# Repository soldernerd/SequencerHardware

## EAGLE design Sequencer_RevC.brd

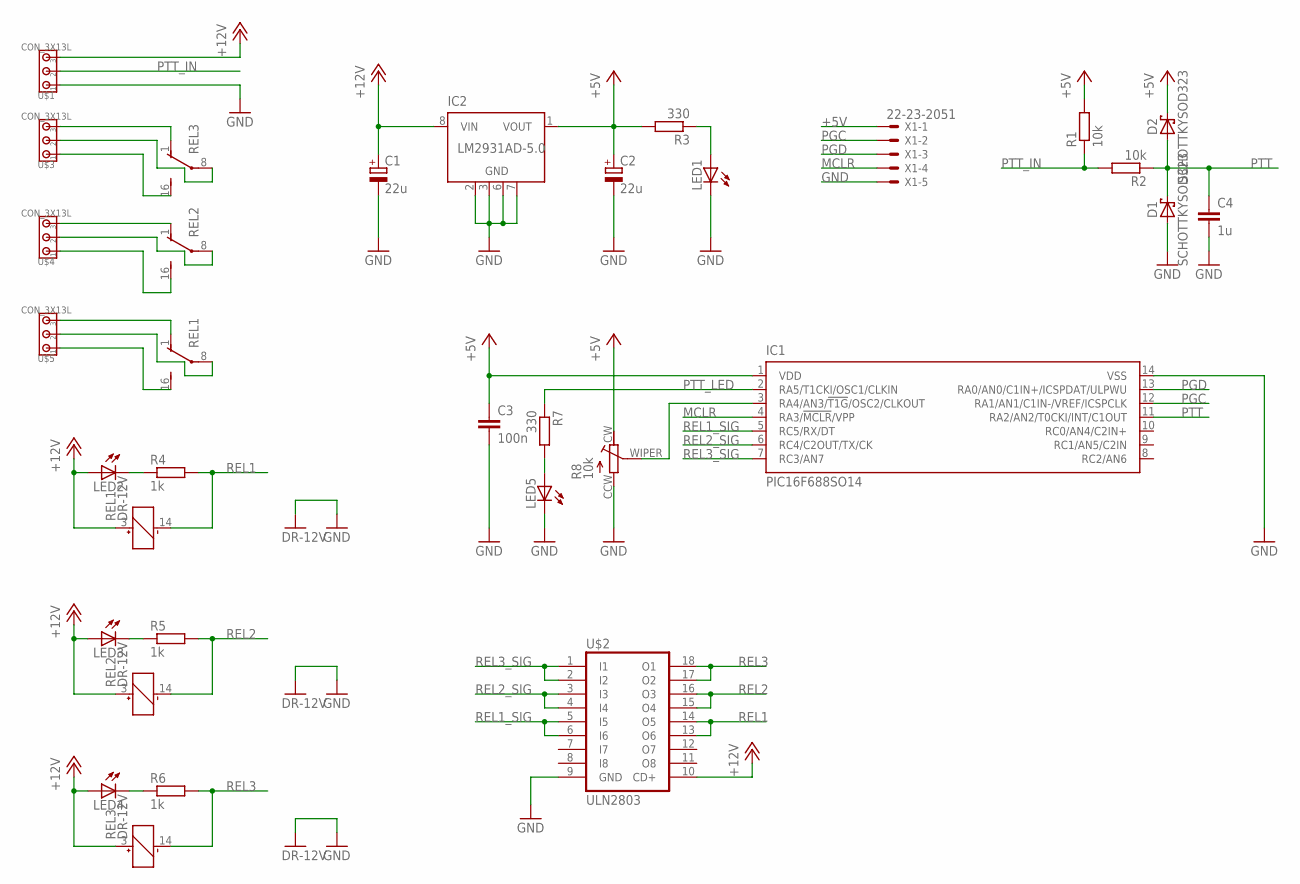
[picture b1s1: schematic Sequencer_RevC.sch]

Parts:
C1, C2: 22u; SMC_C
C3: 100n; C0805
C4: 1u; C0805
D1, D2: SCHOTTKYSOD323; SOD323
IC1: PIC16F688SO14; SO14
IC2: LM2931AD-5.0; SO8
LED1, LED2, LED3, LED4, LED5: LED0805
R1, R2: 10k; R0805
R3, R7: 330; R0805
R4, R5, R6: 1k; R0805
R8: 10k; RTRIM3314G
REL1, REL2, REL3: DR-12V
U$1, U$3, U$4, U$5: CON_3X13L; 200MIL_3X
U$2: ULN2803; SO18W
X1: 22-23-2051

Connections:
+5V: C2.+, C3.1, D2.C, IC1.1 (VDD), IC2.1 (VOUT), R1.2, R3.2, R8.CW, X1.1
+12V: C1.+, IC2.8 (VIN), LED2.A, LED3.A, LED4.A, REL1.3 (+), REL2.3 (+), REL3.3 (+), U$1.3, U$2.10 (CD+)
GND: C1.-, C2.-, C3.2, C4.2, D1.A, IC1.14 (VSS), IC2.2 (GND), IC2.3 (GND), IC2.6 (GND), IC2.7 (GND), LED1.C, LED5.C, R8.CCW, REL1.9 (GND), REL2.9 (GND), REL3.9 (GND), U$1.1, U$2.9 (GND), X1.5
MCLR: IC1.4 (RA3/!MCLR!/VPP), X1.4
unnamed: REL2.16 (S), U$4.1
unnamed: REL2.8, U$4.2
unnamed: REL2.1 (O), U$4.3
unnamed: REL3.8, U$3.2
unnamed: REL1.8, U$5.2
unnamed: REL1.16 (S), U$5.1
unnamed: REL3.16 (S), U$3.1
unnamed: REL3.1 (O), U$3.3
unnamed: IC1.3 (RA4/AN3/!T1G!/OSC2/CLKOUT), R8.WIPER
unnamed: LED1.A, R3.1
unnamed: LED5.A, R7.2
unnamed: REL1.1 (O), U$5.3
unnamed: LED3.C, R5.1
unnamed: LED2.C, R4.1
unnamed: LED4.C, R6.1
PGC: IC1.12 (RA1/AN1/C1IN-/VREF/ICSPCLK), X1.2
PGD: IC1.13 (RA0/AN0/C1IN+/ICSPDAT/ULPWU), X1.3
PTT: C4.1, D1.C, D2.A, IC1.11 (RA2/AN2/T0CKI/INT/C1OUT), R2.1
PTT_IN: R1.1, R2.2, U$1.2
PTT_LED: IC1.2 (RA5/T1CKI/OSC1/CLKIN), R7.1
REL1: R4.2, REL1.14 (-), U$2.13 (O6), U$2.14 (O5)
REL1_SIG: IC1.5 (RC5/RX/DT), U$2.5 (I5), U$2.6 (I6)
REL2: R5.2, REL2.14 (-), U$2.15 (O4), U$2.16 (O3)
REL2_SIG: IC1.6 (RC4/C2OUT/TX/CK), U$2.3 (I3), U$2.4 (I4)
REL3: R6.2, REL3.14 (-), U$2.17 (O2), U$2.18 (O1)
REL3_SIG: IC1.7 (RC3/AN7), U$2.1 (I1), U$2.2 (I2)

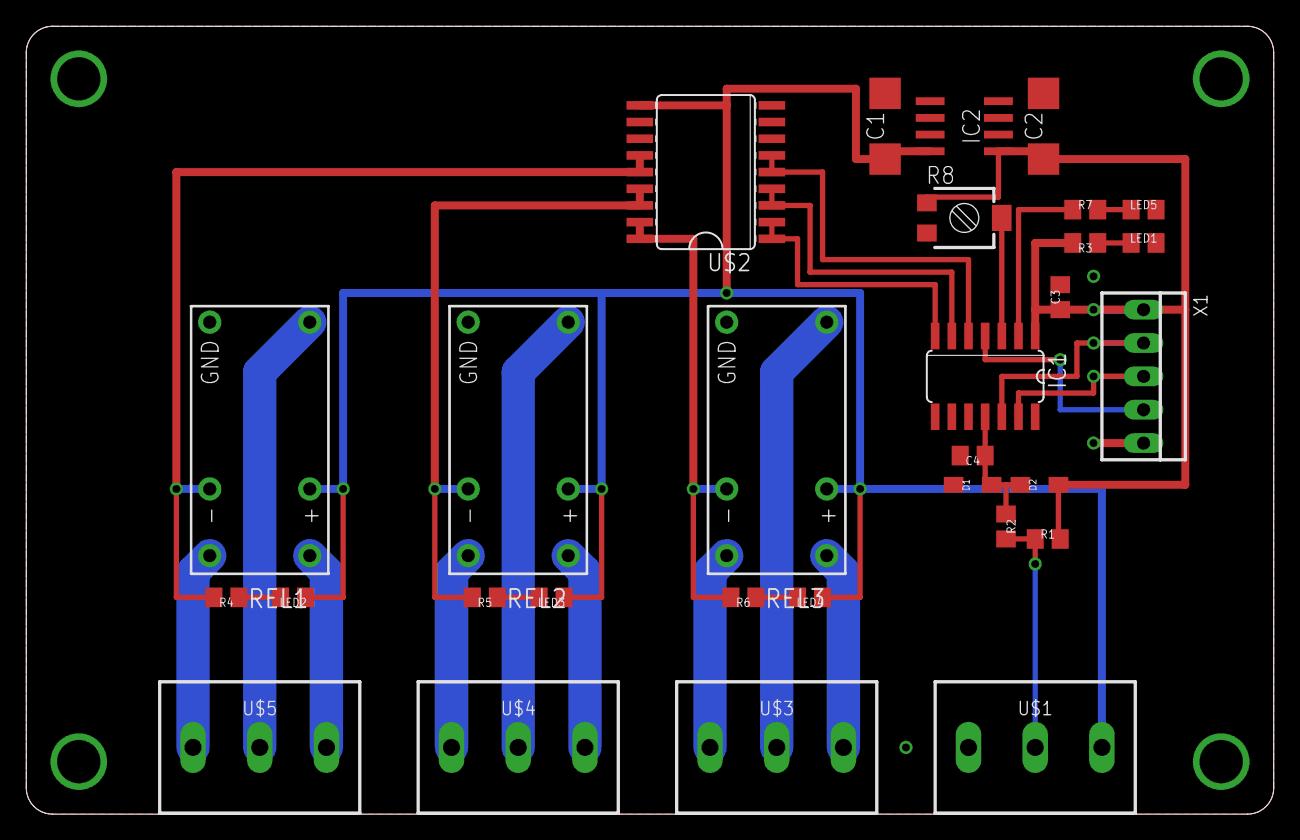
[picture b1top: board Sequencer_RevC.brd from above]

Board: 2 copper layers, 95.0 x 60.0 mm, 30 parts (0 on the bottom side), 30 nets.

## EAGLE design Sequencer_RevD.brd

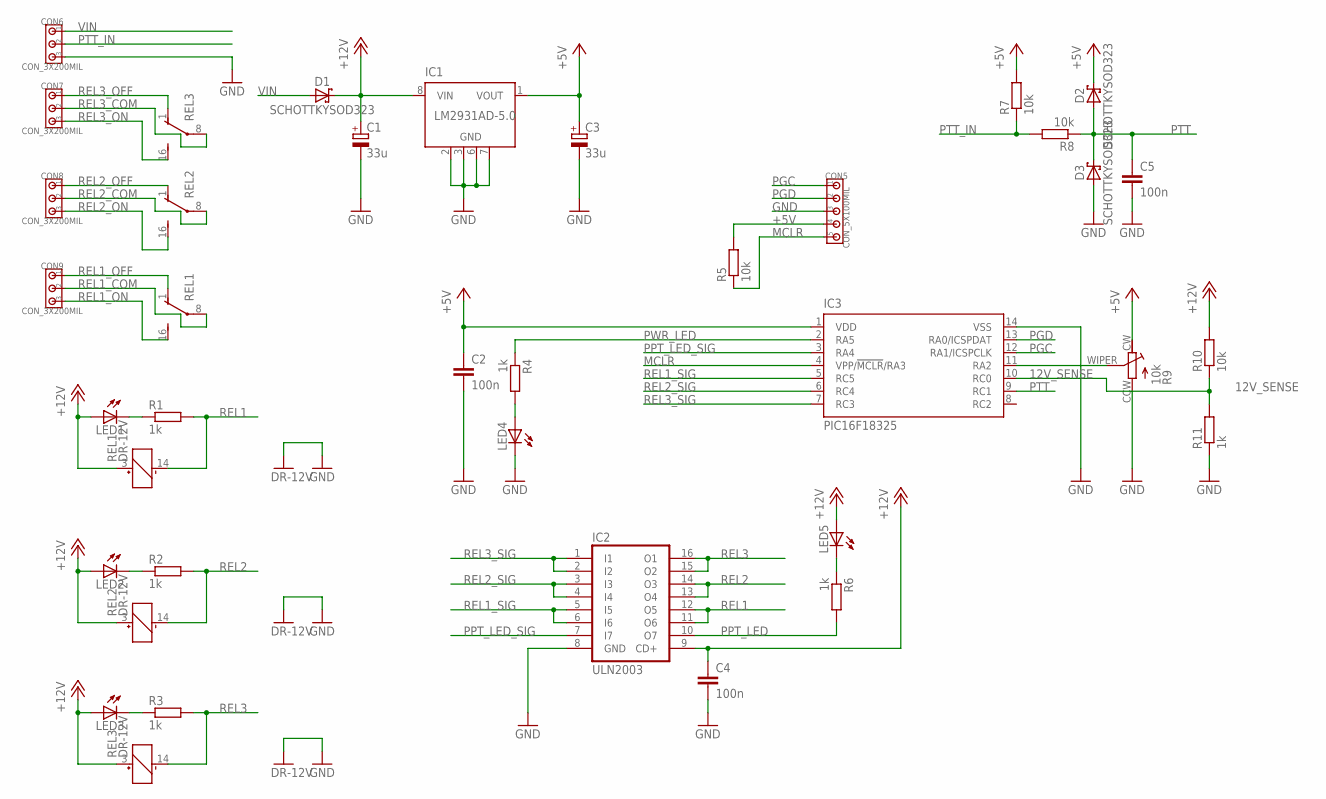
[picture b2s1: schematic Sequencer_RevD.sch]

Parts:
C1, C3: 33u; SMC_C
C2, C4, C5: 100n; C0805
CON5: CON_5X100MIL; 100MIL_5X
CON6, CON7, CON8, CON9: CON_3X200MIL; 200MIL_3X
D1, D2, D3: SCHOTTKYSOD323; SOD323
IC1: LM2931AD-5.0; SOIC8
IC2: ULN2003; SO16
IC3: PIC16F18325; SO14
LED1, LED2, LED3, LED4, LED5: LED0805
R1, R2, R3, R4, R6, R11: 1k; R0805
R5, R7, R8, R10: 10k; R0805
R9: 10k; RTRIM3314G
REL1, REL2, REL3: DR-12V

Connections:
12V_SENSE: IC3.10 (RC0), R10.1, R11.2
+5V: C2.1, C3.+, CON5.4, D2.C, IC1.1 (VOUT), IC3.1 (VDD), R5.2, R7.2, R9.CW
+12V: C1.+, C4.1, D1.C, IC1.8 (VIN), IC2.9 (CD+), LED1.A, LED2.A, LED3.A, LED5.A, R10.2, REL1.3 (+), REL2.3 (+), REL3.3 (+)
GND: C1.-, C2.2, C3.-, C4.2, C5.2, CON5.3, CON6.3, D3.A, IC1.2 (GND), IC1.3 (GND), IC1.6 (GND), IC1.7 (GND), IC2.8 (GND), IC3.14 (VSS), LED4.C, R9.CCW, R11.1, REL1.9 (GND), REL2.9 (GND), REL3.9 (GND)
MCLR: CON5.5, IC3.4 (VPP/!MCLR!/RA3), R5.1
unnamed: IC3.11 (RA2), R9.WIPER
unnamed: LED5.C, R6.1
unnamed: LED4.A, R4.2
unnamed: LED2.C, R2.1
unnamed: LED1.C, R1.1
unnamed: LED3.C, R3.1
PGC: CON5.1, IC3.12 (RA1/ICSPCLK)
PGD: CON5.2, IC3.13 (RA0/ICSPDAT)
PPT_LED: IC2.10 (O7), R6.2
PPT_LED_SIG: IC2.7 (I7), IC3.3 (RA4)
PTT: C5.1, D2.A, D3.C, IC3.9 (RC1), R8.1
PTT_IN: CON6.2, R7.1, R8.2
PWR_LED: IC3.2 (RA5), R4.1
REL1: IC2.11 (O6), IC2.12 (O5), R1.2, REL1.14 (-)
REL1_COM: CON9.2, REL1.8
REL1_OFF: CON9.1, REL1.1 (O)
REL1_ON: CON9.3, REL1.16 (S)
REL1_SIG: IC2.5 (I5), IC2.6 (I6), IC3.5 (RC5)
REL2: IC2.13 (O4), IC2.14 (O3), R2.2, REL2.14 (-)
REL2_COM: CON8.2, REL2.8
REL2_OFF: CON8.1, REL2.1 (O)
REL2_ON: CON8.3, REL2.16 (S)
REL2_SIG: IC2.3 (I3), IC2.4 (I4), IC3.6 (RC4)
REL3: IC2.15 (O2), IC2.16 (O1), R3.2, REL3.14 (-)
REL3_COM: CON7.2, REL3.8
REL3_OFF: CON7.1, REL3.1 (O)
REL3_ON: CON7.3, REL3.16 (S)
REL3_SIG: IC2.1 (I1), IC2.2 (I2), IC3.7 (RC3)
VIN: CON6.1, D1.A

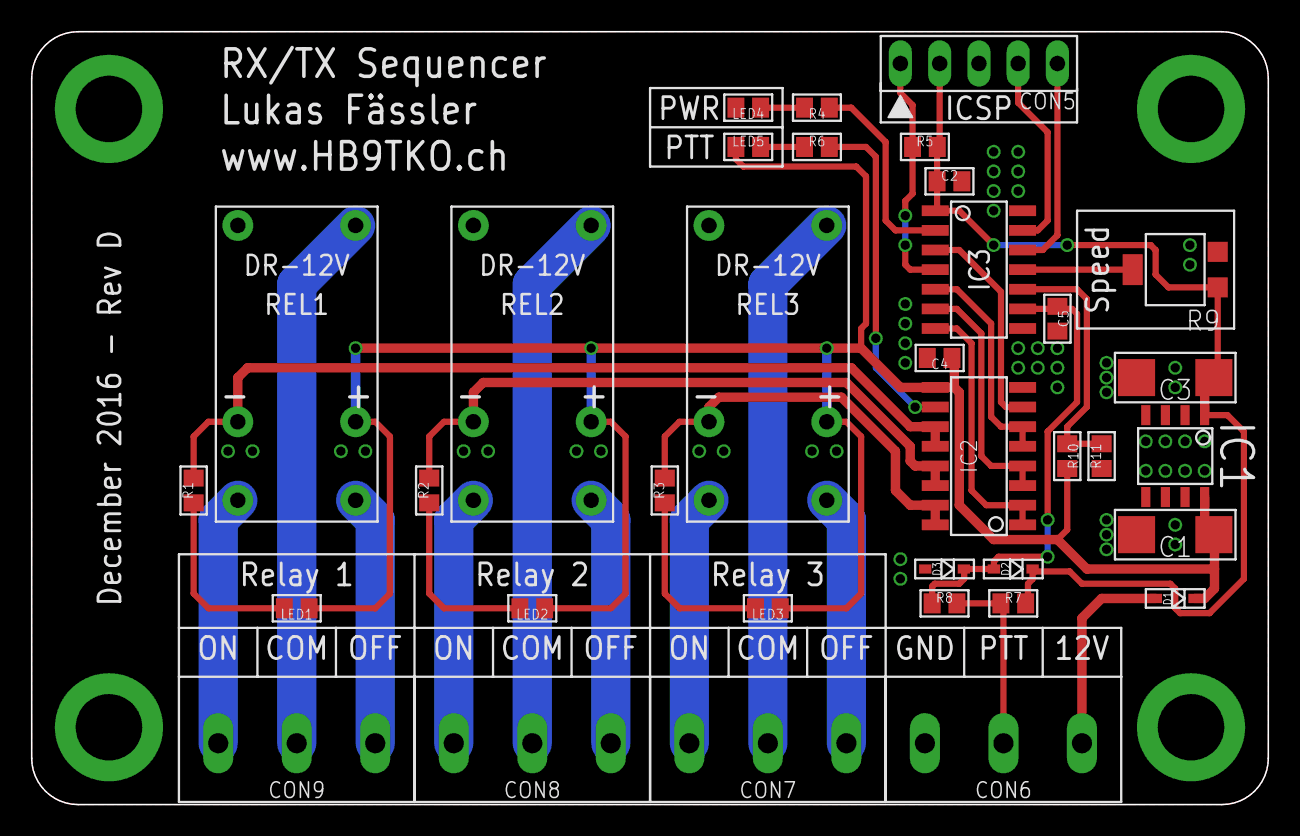
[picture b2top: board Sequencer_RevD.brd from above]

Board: 2 copper layers, 80.0 x 50.0 mm, 35 parts (0 on the bottom side), 34 nets.

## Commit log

2017-01-07 Initital Commit
